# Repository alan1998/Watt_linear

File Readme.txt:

Watt meter
Linear power supply! (from 36v?)
SAM D20 with i2c and serial ports
Temp monitor on board and external
3.3v out

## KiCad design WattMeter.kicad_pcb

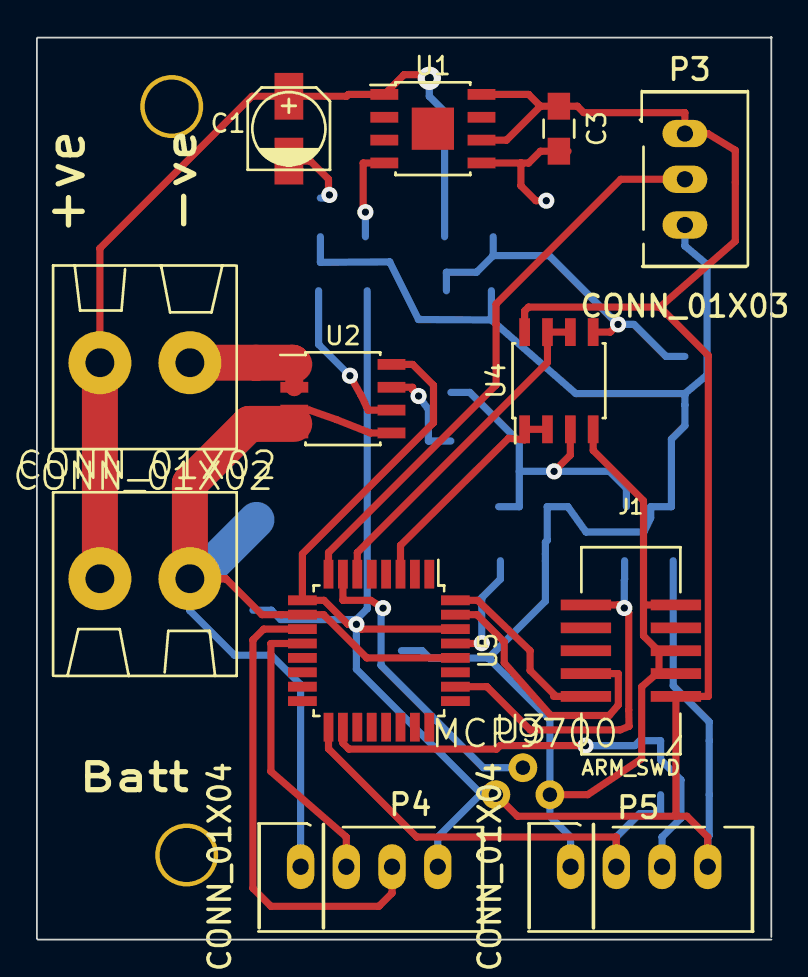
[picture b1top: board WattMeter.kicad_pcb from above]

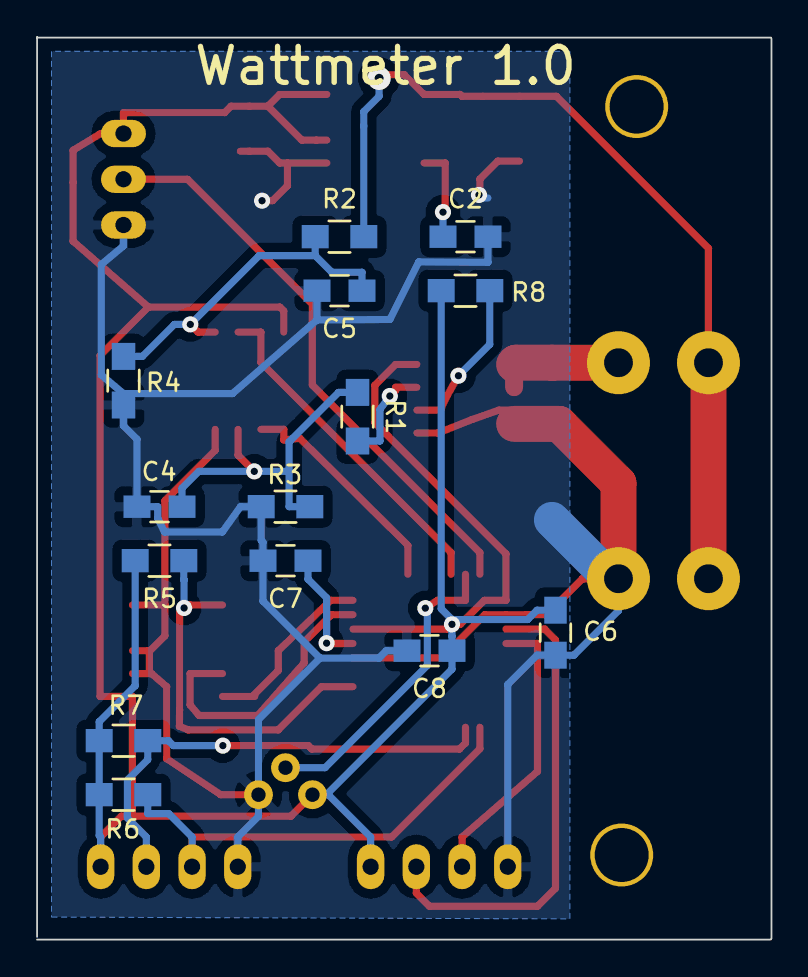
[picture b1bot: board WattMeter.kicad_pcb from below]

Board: 2 copper layers, 40.8 x 50.2 mm, 29 parts (14 on the bottom side), 21 nets.

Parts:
3mm, 3mm#2: VAL**; 3mm_mount
C1: 1uF; c_elec_4x4.5
C2, C6, C7, C8: 0.1uF; C_0805_HandSoldering
C3: 10uF; C_0805_HandSoldering
C4: 6u8; C_0805_HandSoldering
C5: 4u7; C_0805_HandSoldering
J1: ARM_SWD; 2x5_50mil_SMD
P1, P2: CONN_01X02; TermBlock2Pos
P3: CONN_01X03; JST-XH3
P4, P5: CONN_01X04; JST-XH4
R1: 3.3k; R_0805_HandSoldering
R2: 48k; R_0805_HandSoldering
R3: 6.7K; R_0805_HandSoldering
R4: 2K; R_0805_HandSoldering
R5, R6, R7, R8: 10k; R_0805_HandSoldering
U1: MAQ5283; SOIC-8-1EP_3.9x4.9mm_Pitch1.27mm
U2: ACS711; SOIC-8_3.9x4.9mm_Pitch1.27mm
U3: MCP9700; TO-92
U4: MCP6002; SOIC-8_3.9x4.9mm_Pitch1.27mm
U5: SAMD20E15A-A; TQFP-32_7x7mm_Pitch0.8mm

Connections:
/AT1: U3.2, U5.7
/AT2: P3.2, U5.8
/Acurr: U4.1, U4.2, U5.3
/Avolt: U4.6, U4.7, U5.6
/BP: C1.1, P1.2, P2.1, R2.2, U1.1
/CN: P1.1, U2.1, U2.2
/RST: J1.10, R5.1, U5.26
/Rx: P4.2, U5.12
/SCL: P5.3, R7.2, U5.18
/SDA: P5.2, R6.2, U5.17
/SWCK: J1.4, U5.31
/SWD: J1.2, U5.32
/Tx: P4.3, U5.11
/V33: C3.1, C6.1, C8.1, J1.1, P3.3, P4.4, P5.4, R5.2, R6.1, R7.1, R8.1, U1.6, U1.8, U2.8, U3.1, U4.8, U5.9, U5.30
GND: C1.2, C2.2, C3.2, C4.2, C5.2, C6.2, C7.2, C8.2, J1.3, J1.5, J1.9, P2.2, P3.1, P4.1, P5.1, R3.2, R4.2, U1.5, U2.3, U2.4, U2.5, U3.3, U4.4, U5.10, U5.28
unnamed: C2.1, U1.4
unnamed: C4.1, R1.1, R3.1, U4.3
unnamed: C5.1, R2.1, R4.1, U4.5
unnamed: C7.1, U5.29
unnamed: R1.2, U2.7
unnamed: R8.2, U2.6

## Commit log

2015-05-23 start
2015-05-28 All compnents on schematic. PCCMP not done
2015-05-30 Raw Autoroute
2015-05-30 Fixed some autoroute
2015-06-09 Parts
2015-07-19 micro python+
